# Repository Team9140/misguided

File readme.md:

# Misguided

The Misguided HAT is a HAT designed for the Raspbery Pi 5 that adds a 12v power input, CAN FD, a Digital input for time syncronization and a Hailo Neural Accelerator card

It is inteded for the FIRST Robotics competion as part of a RPI based vision subsytem

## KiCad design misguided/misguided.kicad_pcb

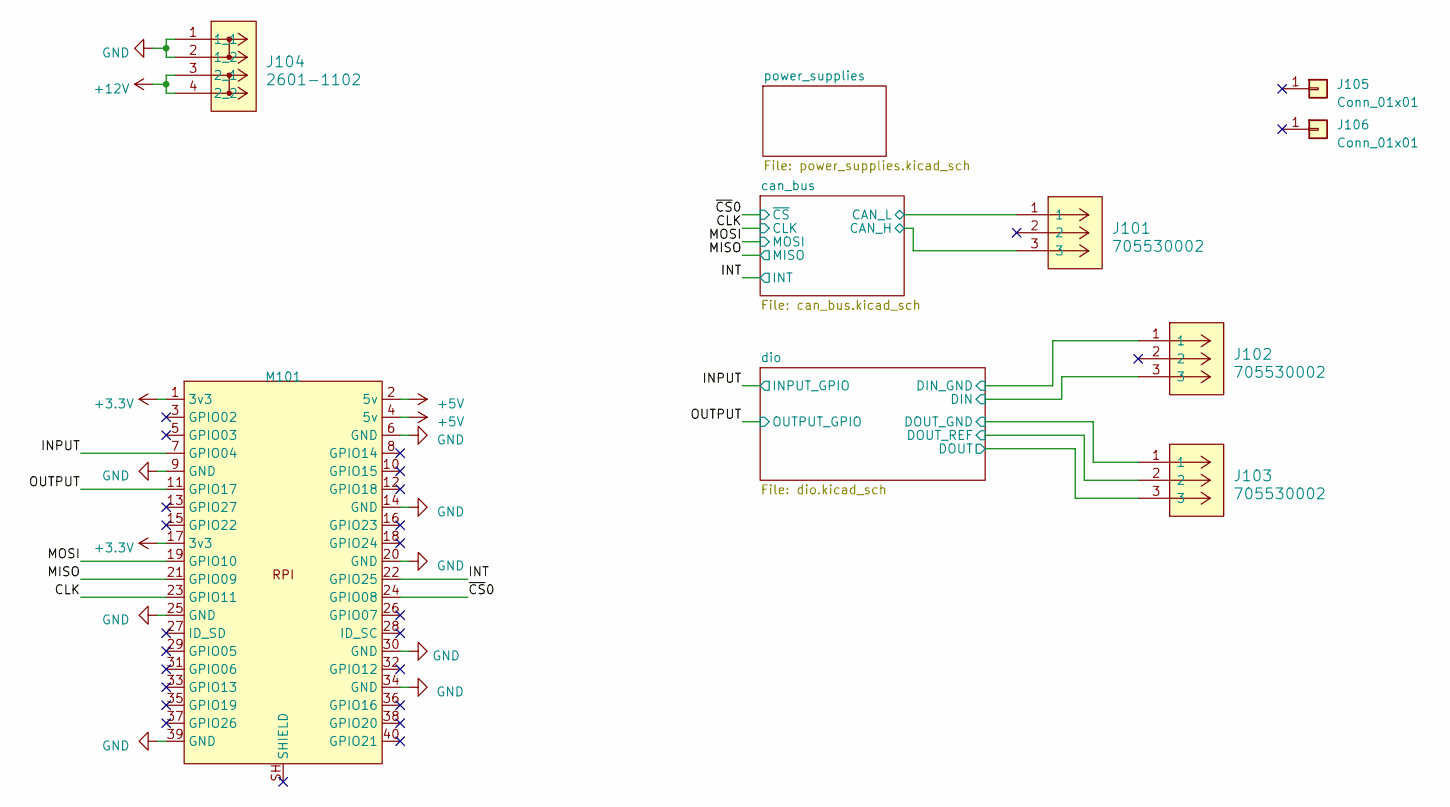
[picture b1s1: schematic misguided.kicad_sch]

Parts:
J101, J102, J103: 705530002; CONN_705530002_03_MOL
J104: 2601-1102; CONN2_2601-1102_WAG
J105: Conn_01x01; lotion_on_head
J106: Conn_01x01; robobots
M101: pi_hat

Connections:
+3.3V: M101.1 (3v3), M101.17 (3v3); also elsewhere on the board
+5V: M101.2 (5v), M101.4 (5v); also elsewhere on the board
+12V: J104.3 (2_1), J104.4 (2_2); also elsewhere on the board
/CLK: M101.23 (GPIO11); also elsewhere on the board
/INPUT: M101.7 (GPIO04); also elsewhere on the board
/INT: M101.22 (GPIO25); also elsewhere on the board
/MISO: M101.21 (GPIO09); also elsewhere on the board
/MOSI: M101.19 (GPIO10); also elsewhere on the board
/OUTPUT: M101.11 (GPIO17); also elsewhere on the board
/can_bus/can_N: J101.1; also elsewhere on the board
/can_bus/can_P: J101.3; also elsewhere on the board
/dio/DIN: J102.3; also elsewhere on the board
/dio/DIN_GND: J102.1; also elsewhere on the board
/dio/DOUT: J103.3; also elsewhere on the board
/dio/DOUT_GND: J103.1; also elsewhere on the board
/dio/DOUT_REF: J103.2; also elsewhere on the board
/~CS0: M101.24 (GPIO08); also elsewhere on the board
GND: J104.1 (1_1), J104.2 (1_2), M101.6 (GND), M101.9 (GND), M101.14 (GND), M101.20 (GND), M101.25 (GND), M101.30 (GND), M101.34 (GND), M101.39 (GND); also elsewhere on the board

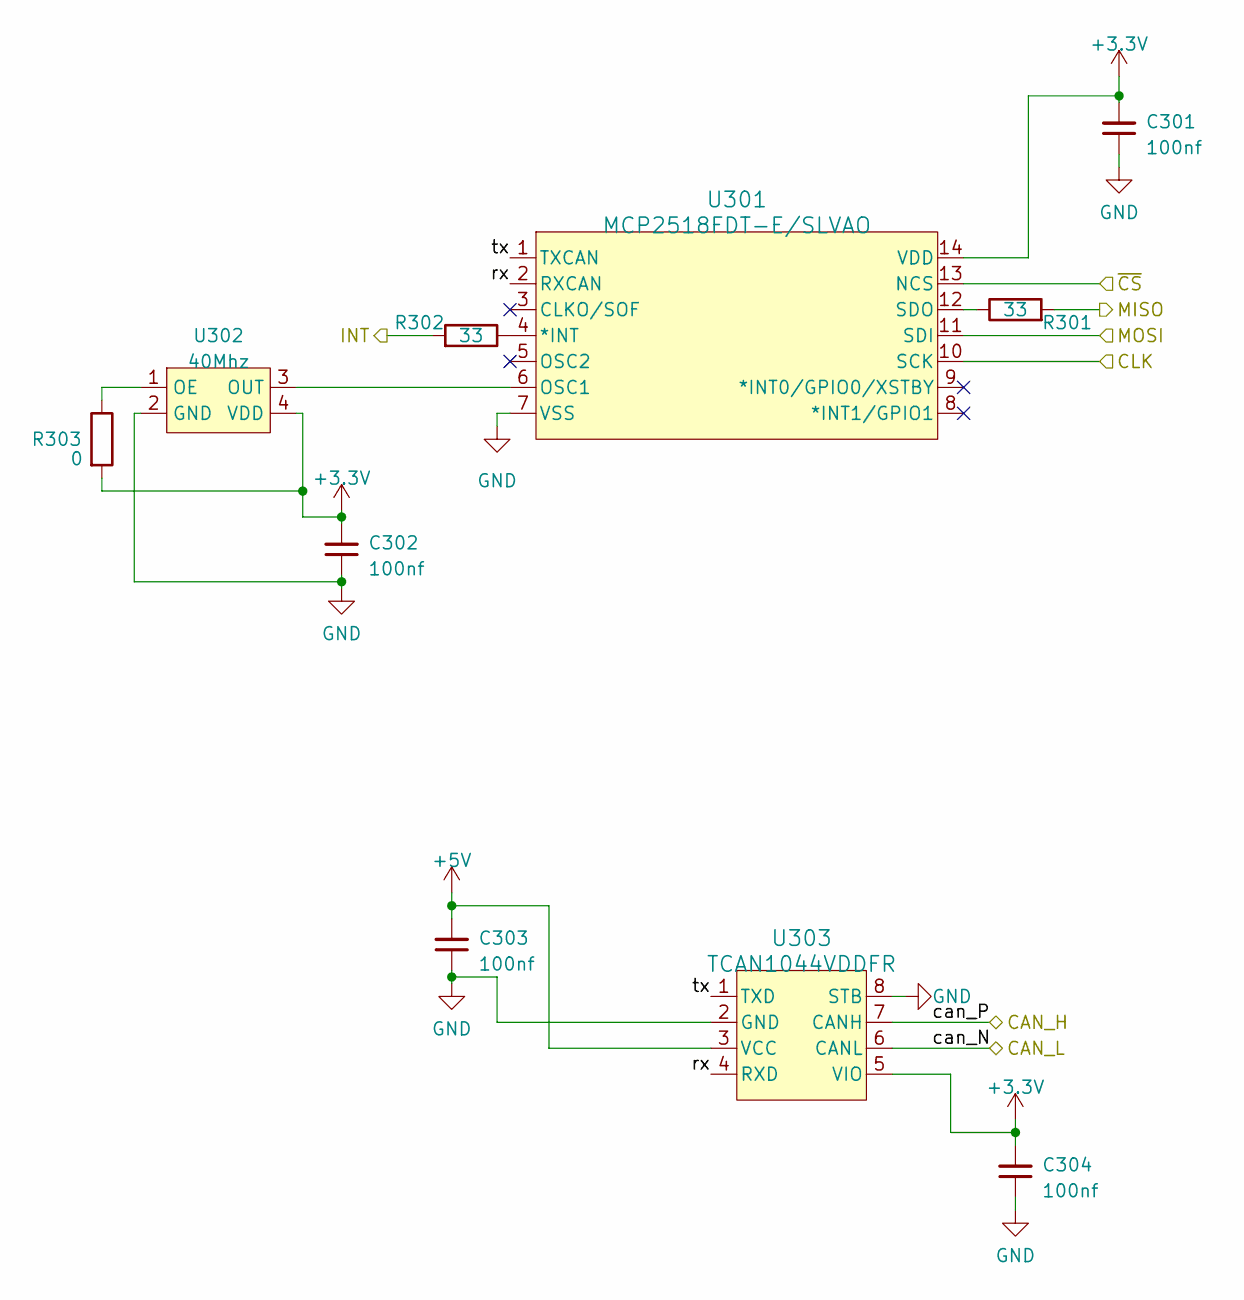
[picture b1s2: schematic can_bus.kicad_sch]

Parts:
C301, C302, C303, C304: 100nf; C_0402_1005Metric
R301, R302: 33; R_0402_1005Metric
R303: 0; R_0402_1005Metric
U301: MCP2518FDT-E/SLVAO; SOIC14_SL_MCH
U302: 40Mhz; Oscillator_SMD_Abracon_ASE-4Pin_3.2x2.5mm
U303: TCAN1044VDDFR; SOT-23-THIN-8_DDF_TEX

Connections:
+3.3V: C301.2, C302.2, C304.2, R303.2, U301.14 (VDD), U302.4 (VDD), U303.5 (VIO); also elsewhere on the board
+5V: C303.2, U303.3 (VCC); also elsewhere on the board
/CLK: U301.10 (SCK); also elsewhere on the board
/INT: R302.2; also elsewhere on the board
/MISO: R301.2; also elsewhere on the board
/MOSI: U301.11 (SDI); also elsewhere on the board
/can_bus/can_N: U303.6 (CANL); also elsewhere on the board
/can_bus/can_P: U303.7 (CANH); also elsewhere on the board
/can_bus/rx: U301.2 (RXCAN), U303.4 (RXD)
/can_bus/tx: U301.1 (TXCAN), U303.1 (TXD)
/~CS0: U301.13 (NCS); also elsewhere on the board
GND: C301.1, C302.1, C303.1, C304.1, U301.7 (VSS), U302.2 (GND), U303.2 (GND), U303.8 (STB); also elsewhere on the board
unnamed: R302.1, U301.4 (*INT)
unnamed: U301.6 (OSC1), U302.3 (OUT)
unnamed: R301.1, U301.12 (SDO)
unnamed: R303.1, U302.1 (OE)

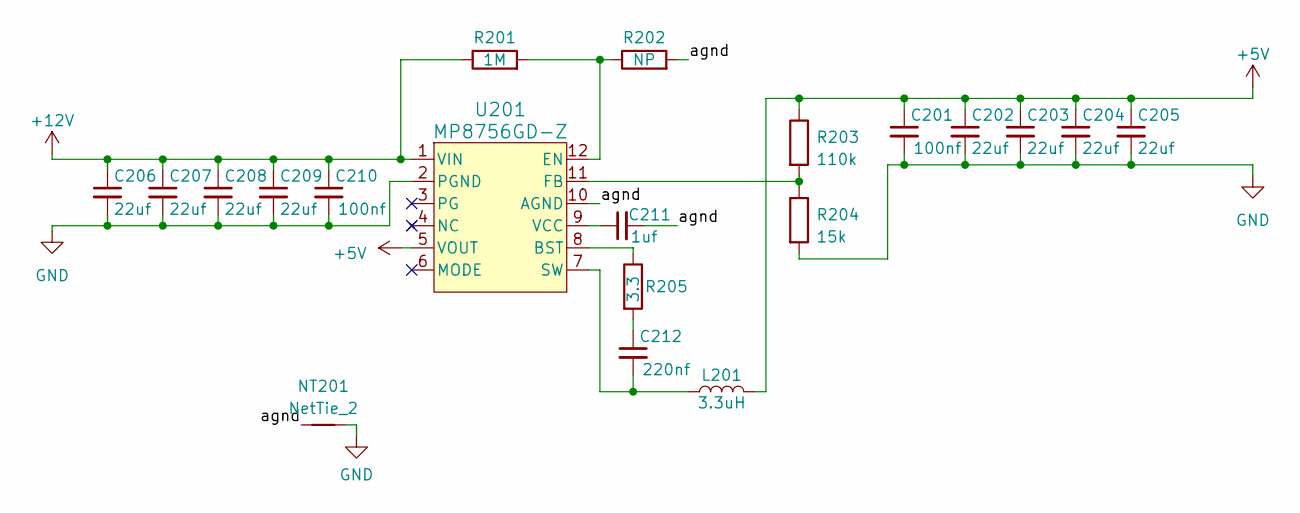
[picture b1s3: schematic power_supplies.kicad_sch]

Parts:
C201, C210: 100nf; C_0603_1608Metric
C202, C203, C204, C205, C206, C207, C208, C209: 22uf; C_0805_2012Metric
C211: 1uf; C_0603_1608Metric
C212: 220nf; C_0402_1005Metric
L201: 3.3uH; IND_CYA0630_SHH; PartNumber CYA0630-3.3UH
NT201: NetTie_2; NetTie-2_SMD_Pad0.5mm
R201: 1M; R_0402_1005Metric
R202: NP; R_0402_1005Metric
R203: 110k; R_0402_1005Metric
R204: 15k; R_0402_1005Metric
R205: 3.3; R_0402_1005Metric
U201: MP8756GD-Z; QFN-12_MP8756_MNP

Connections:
+5V: C201.1, C202.1, C203.1, C204.1, C205.1, L201.2, R203.1, U201.5 (VOUT); also elsewhere on the board
+12V: C206.1, C207.1, C208.1, C209.1, C210.1, R201.1, U201.1 (VIN); also elsewhere on the board
/power_supplies/agnd: C211.2, NT201.1, R202.2, U201.10 (AGND)
GND: C201.2, C202.2, C203.2, C204.2, C205.2, C206.2, C207.2, C208.2, C209.2, C210.2, NT201.2, R204.2, U201.2 (PGND); also elsewhere on the board
unnamed: C212.1, R205.2
unnamed: R205.1, U201.8 (BST)
unnamed: R201.2, R202.1, U201.12 (EN)
unnamed: R203.2, R204.1, U201.11 (FB)
unnamed: C212.2, L201.1, U201.7 (SW)
unnamed: C211.1, U201.9 (VCC)

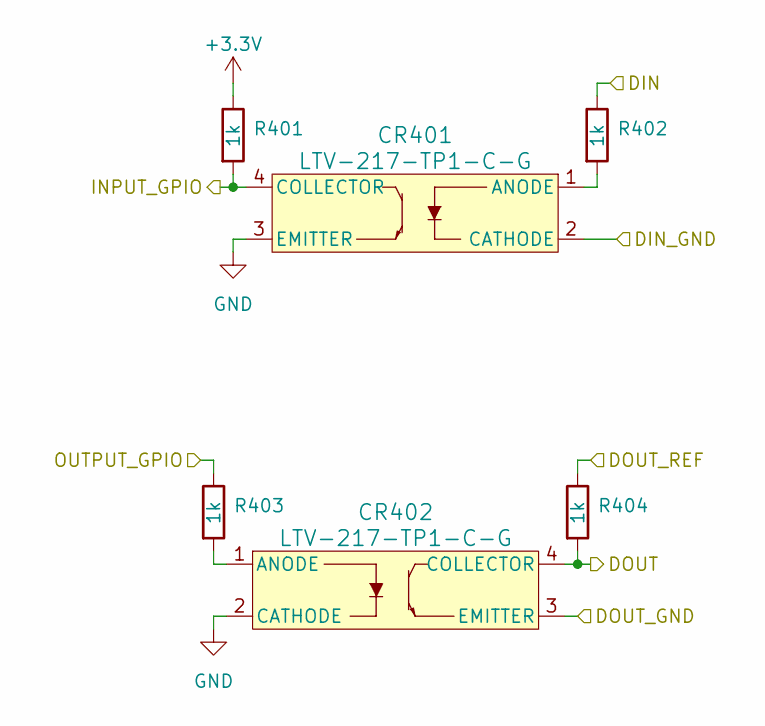
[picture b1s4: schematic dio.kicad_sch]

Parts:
CR401, CR402: LTV-217-TP1-C-G; LTV_217_LTO
R401, R402, R403, R404: 1k; R_0603_1608Metric

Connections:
+3.3V: R401.1; also elsewhere on the board
/INPUT: CR401.4 (COLLECTOR), R401.2; also elsewhere on the board
/OUTPUT: R403.1; also elsewhere on the board
/dio/DIN: R402.1; also elsewhere on the board
/dio/DIN_GND: CR401.2 (CATHODE); also elsewhere on the board
/dio/DOUT: CR402.4 (COLLECTOR), R404.2; also elsewhere on the board
/dio/DOUT_GND: CR402.3 (EMITTER); also elsewhere on the board
/dio/DOUT_REF: R404.1; also elsewhere on the board
GND: CR401.3 (EMITTER), CR402.2 (CATHODE); also elsewhere on the board
unnamed: CR401.1 (ANODE), R402.2
unnamed: CR402.1 (ANODE), R403.2

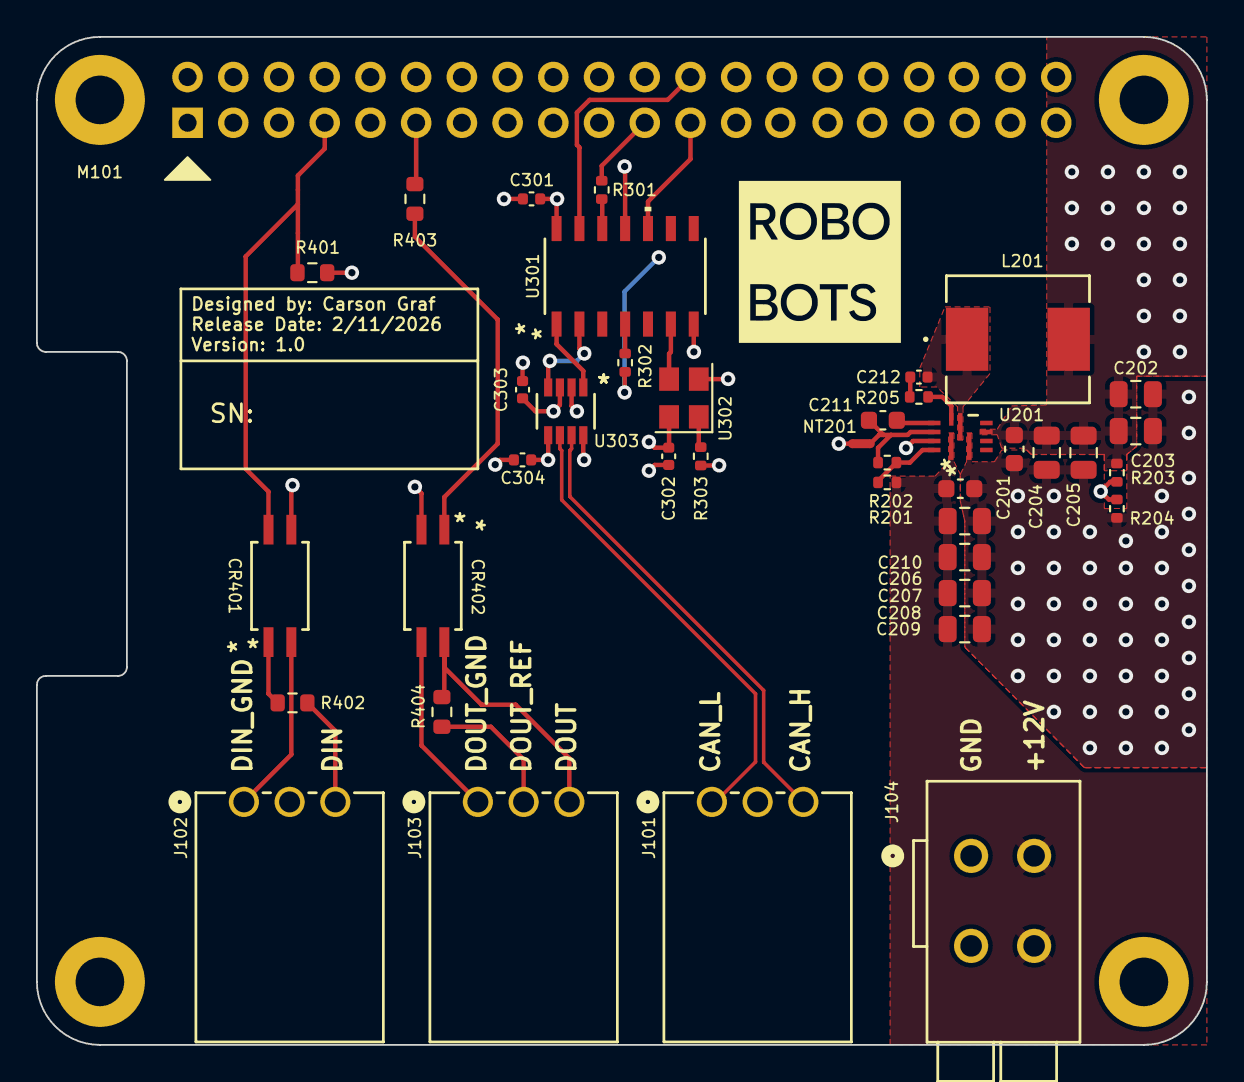
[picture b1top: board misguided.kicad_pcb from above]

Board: 4 copper layers, 65.0 x 56.0 mm, 43 parts (1 on the bottom side), 33 nets.

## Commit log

2025-12-13 Added requirements
2025-12-13 Initial readme
2025-12-13 started bare Kicad project
2025-12-13 started bare Kicad project (#2)
2025-12-14 added subsheets
2025-12-15 added some symbols
2025-12-15 added git ignore
2025-12-15 added git ignore (#3)
2025-12-15 fixing ignored stuff
2025-12-15 cleaning up artifacts
2025-12-15 added datasheets
2026-01-10 buncha stuff
2026-02-01 more setup
2026-02-01 Config project (#4)
    * started bare Kicad project
    * added subsheets
    * added some symbols
    * cleaning up artifacts
    * added datasheets
    * buncha stuff
2026-02-01 various fixes
2026-02-07 schematic finished
2026-02-07 fixed schematic associations
2026-02-08 fixed schematic associations (#5)
2026-02-12 layed out and ordered
